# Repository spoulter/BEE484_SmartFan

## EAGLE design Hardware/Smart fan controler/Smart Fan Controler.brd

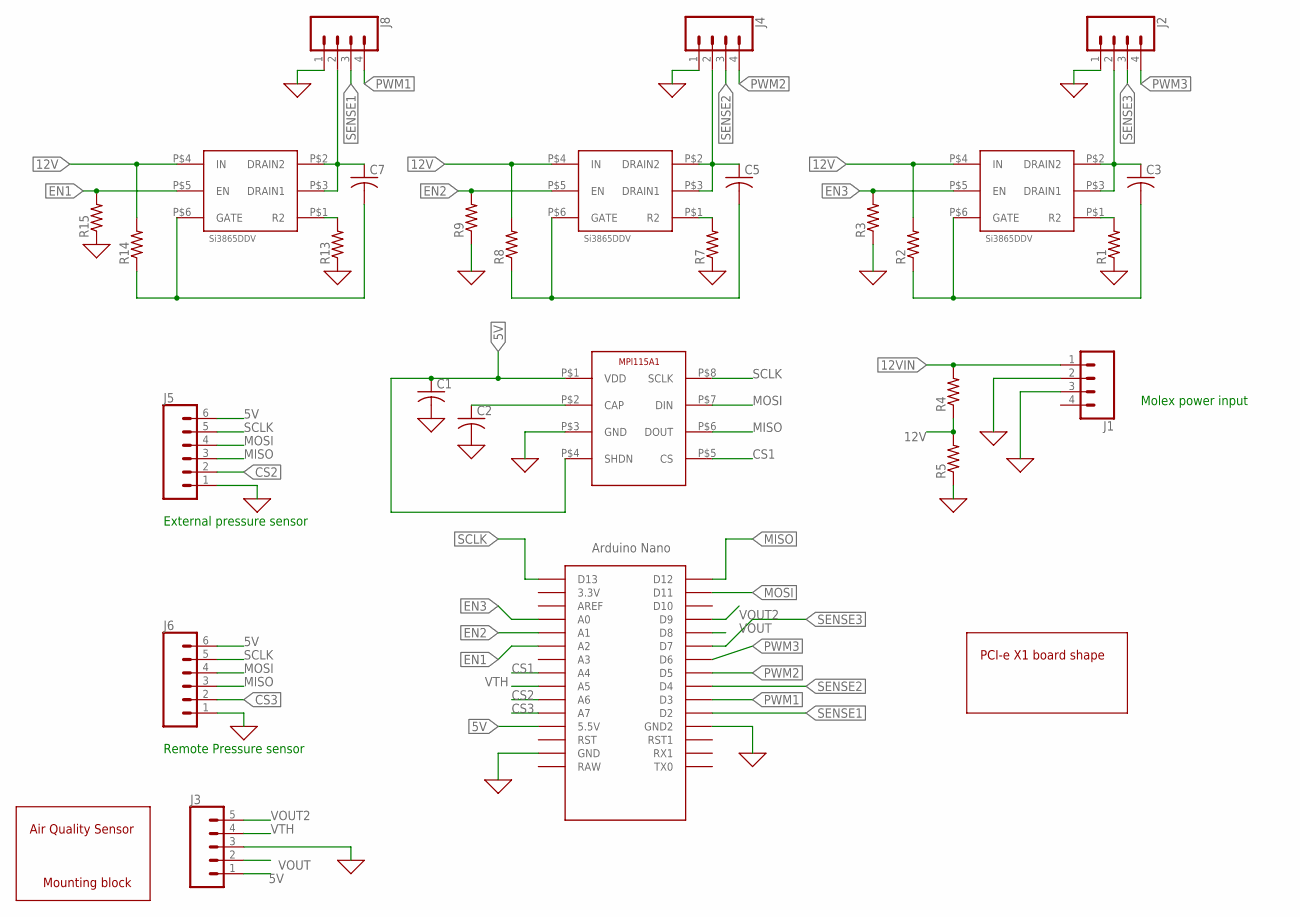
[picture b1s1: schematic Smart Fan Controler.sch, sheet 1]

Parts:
C1, C2, C3, C5, C7: C-USC0805; C0805
J1, J2, J4, J8: CONN_04MOLEX_FAN_HEADER; MOLEX_FAN_HEADER
J3: CONN_05NO_SILK; 1X05_NO_SILK
J5, J6: CONN_06LOCK_LONGPADS; 1X06_LOCK_LONGPADS
R1, R2, R3, R4, R5, R7, R8, R9, R13, R14, R15: R-US_R0805; R0805
U$1: MPL115A1
U$2: NANO
U$3, U$5, U$8: SI3865DDV; TSOP-6
U$4: AIR_QUALITY_SENSOR; AIR_SENSOR

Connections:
0: C1.2, C2.2, J1.2, J1.3, J2.1, J3.3, J4.1, J5.1, J6.1, J8.1, R1.1, R3.1, R5.1, R7.1, R9.1, R13.1, R15.1, U$1.P$3 (GND), U$2.GND, U$2.GND1 (GND2); also elsewhere on the board
5V: C1.1, J3.1, J5.6, J6.6, U$1.P$1 (VDD), U$1.P$4 (SHDN), U$2.5V (5.5V); also elsewhere on the board
12V: R2.2, R4.1, R5.2, R8.2, R14.2, U$3.P$4 (IN), U$5.P$4 (IN), U$8.P$4 (IN)
12VIN: J1.1, R4.2
CS1: U$1.P$5 (CS), U$2.A4
CS2: J5.2, U$2.A6
CS3: J6.2, U$2.A7
EN1: R15.2, U$2.A2, U$8.P$5 (EN)
EN2: R9.2, U$2.A1, U$5.P$5 (EN)
EN3: R3.2, U$2.A0, U$3.P$5 (EN)
MISO: J5.3, J6.3, U$1.P$6 (DOUT), U$2.D12; also elsewhere on the board
MOSI: J5.4, J6.4, U$1.P$7 (DIN), U$2.D11; also elsewhere on the board
unnamed: C2.1, U$1.P$2 (CAP)
unnamed: R1.2, U$3.P$1 (R2)
unnamed: R7.2, U$5.P$1 (R2)
unnamed: C3.1, J2.2, U$3.P$2 (DRAIN2), U$3.P$3 (DRAIN1)
unnamed: C3.2, R2.1, U$3.P$6 (GATE)
unnamed: C5.1, J4.2, U$5.P$2 (DRAIN2), U$5.P$3 (DRAIN1)
unnamed: C5.2, R8.1, U$5.P$6 (GATE)
unnamed: R13.2, U$8.P$1 (R2)
unnamed: C7.1, J8.2, U$8.P$2 (DRAIN2), U$8.P$3 (DRAIN1)
unnamed: C7.2, R14.1, U$8.P$6 (GATE)
PWM1: J8.4, U$2.D3
PWM2: J4.4, U$2.D5
PWM3: J2.4, U$2.D6
SCLK: J5.5, J6.5, U$1.P$8 (SCLK), U$2.D13; also elsewhere on the board
SENSE1: J8.3, U$2.D2
SENSE2: J4.3, U$2.D4
SENSE3: J2.3, U$2.D7
VOUT: J3.2, U$2.D8
VOUT2: J3.5, U$2.D9
VTH: J3.4, U$2.A5

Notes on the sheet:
Molex power input
Remote Pressure sensor
External pressure sensor
PCI-e X1 board shape

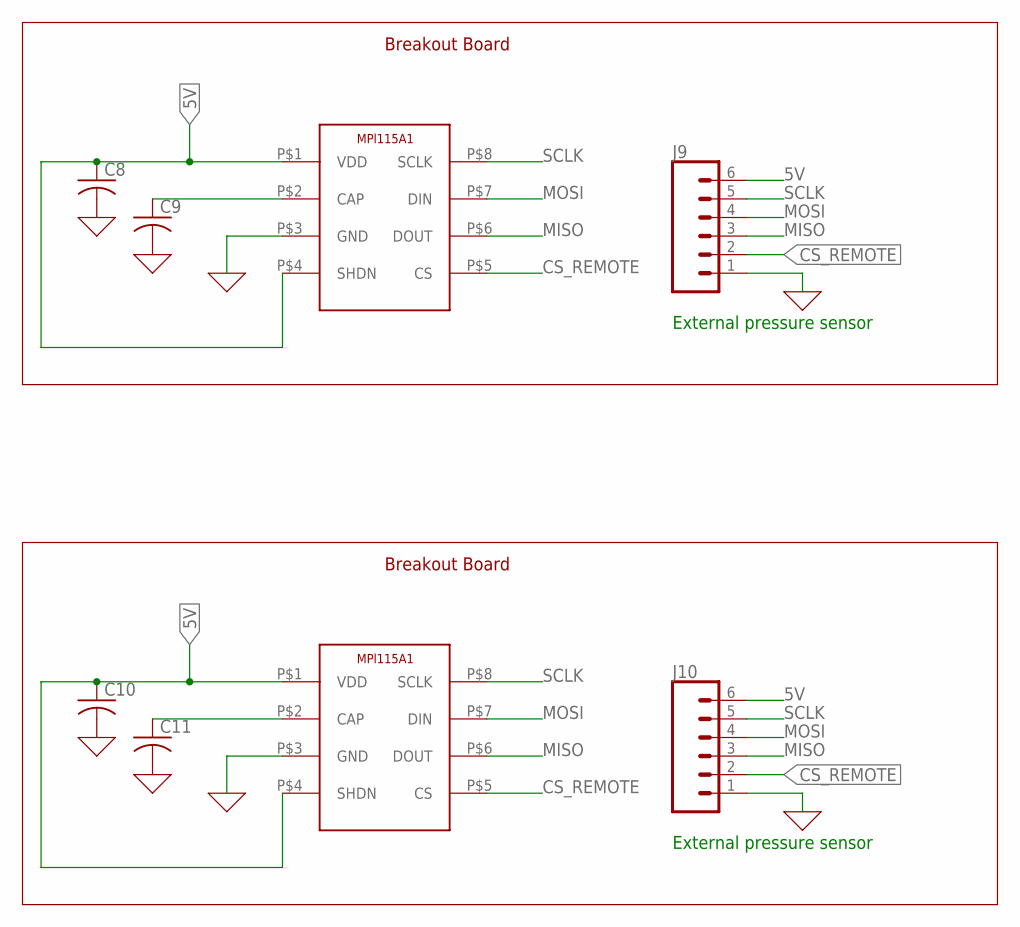
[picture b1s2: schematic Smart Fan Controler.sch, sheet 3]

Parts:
C8, C9, C10, C11: C-USC0805; C0805
J9, J10: CONN_06LOCK_LONGPADS; 1X06_LOCK_LONGPADS
U$7, U$9: MPL115A1

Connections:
0: C8.2, C9.2, C10.2, C11.2, J9.1, J10.1, U$7.P$3 (GND), U$9.P$3 (GND); also elsewhere on the board
5V: C8.1, C10.1, J9.6, J10.6, U$7.P$1 (VDD), U$7.P$4 (SHDN), U$9.P$1 (VDD), U$9.P$4 (SHDN); also elsewhere on the board
CS_REMOTE: J9.2, J10.2, U$7.P$5 (CS), U$9.P$5 (CS)
MISO: J9.3, J10.3, U$7.P$6 (DOUT), U$9.P$6 (DOUT); also elsewhere on the board
MOSI: J9.4, J10.4, U$7.P$7 (DIN), U$9.P$7 (DIN); also elsewhere on the board
unnamed: C9.1, U$7.P$2 (CAP)
unnamed: C11.1, U$9.P$2 (CAP)
SCLK: J9.5, J10.5, U$7.P$8 (SCLK), U$9.P$8 (SCLK); also elsewhere on the board

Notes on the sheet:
External pressure sensor
Breakout Board

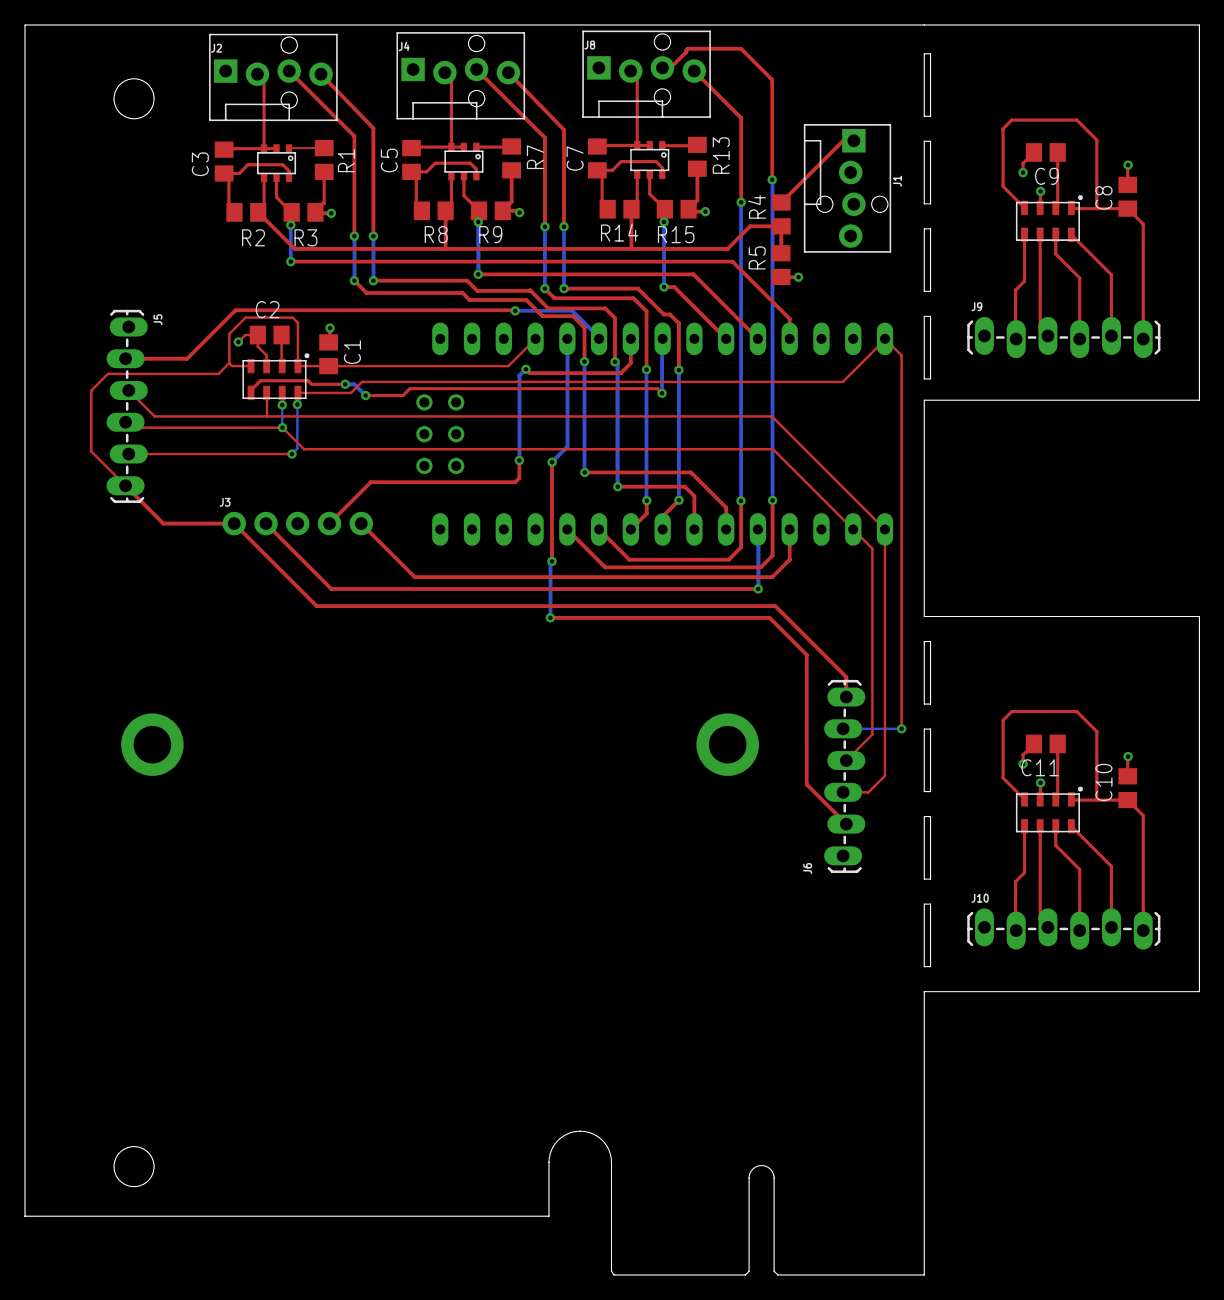
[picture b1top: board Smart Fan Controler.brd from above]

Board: 2 copper layers, 93.9 x 100.0 mm, 37 parts (1 on the bottom side), 35 nets.

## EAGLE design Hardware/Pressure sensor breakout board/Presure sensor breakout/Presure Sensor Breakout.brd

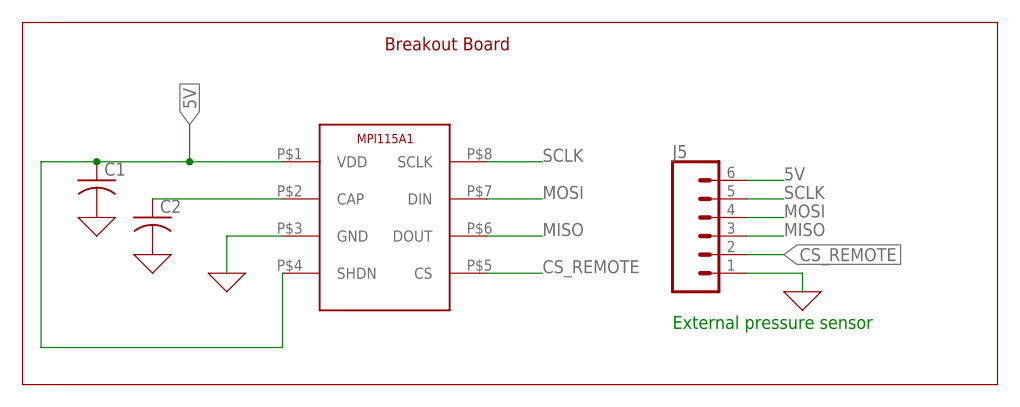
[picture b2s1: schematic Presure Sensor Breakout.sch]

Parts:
C1, C2: C-USC0805; C0805
J5: CONN_06LOCK_LONGPADS; 1X06_LOCK_LONGPADS
U$1: MPL115A1

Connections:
0: C1.2, C2.2, J5.1, U$1.P$3 (GND)
5V: C1.1, J5.6, U$1.P$1 (VDD), U$1.P$4 (SHDN)
CS_REMOTE: J5.2, U$1.P$5 (CS)
MISO: J5.3, U$1.P$6 (DOUT)
MOSI: J5.4, U$1.P$7 (DIN)
unnamed: C2.1, U$1.P$2 (CAP)
SCLK: J5.5, U$1.P$8 (SCLK)

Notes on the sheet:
External pressure sensor
Breakout Board

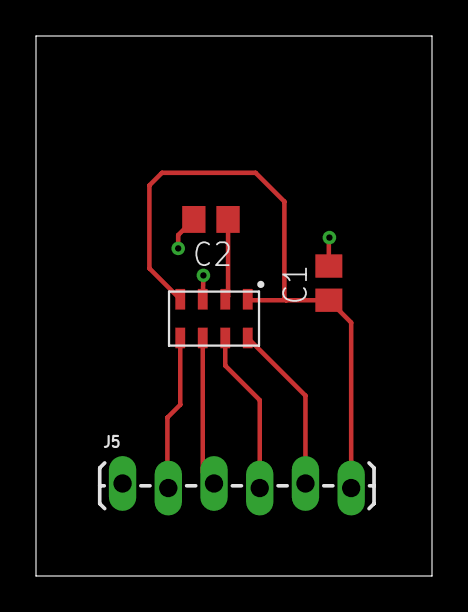
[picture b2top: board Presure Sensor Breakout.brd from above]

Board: 2 copper layers, 22.0 x 30.0 mm, 4 parts (0 on the bottom side), 7 nets.

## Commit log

2018-10-05 Created eagle project file and library. Schemeatic mostly finished
2018-10-05 Reorganized. and added power switch to library
2018-10-06 added datasheet and Bill of Materials
2018-10-06 Removed temporary library
2018-10-06 no message
2018-10-07 Added 3d packages for nano and Fan header. corrected fan header footprint.
2018-10-07 started work on board
2018-10-07 Found fan header in digikey.
2018-10-09 Added 3d model to sensor and fixed fan header 3d model.
2018-10-09 Updated BOM
2018-10-10 Added Mounting holes for bracket
2018-10-11 added 3d models
2018-10-11 Final BOM
2018-10-11 Main board Done
2018-10-12 added stuff.
2018-10-12 added stuff
2018-10-12 added breakout board
2018-10-12 Finalized board
2018-10-12 Added gerber files.
2018-10-18 Finalized board and made gerber files
2018-10-18 uploading version of BOM that was submitted to professor.
2018-10-30 Added Arduino Pin connection refference to software folder
2018-10-30 Added legend to clarify pin connections
2018-11-07 Create Found this online

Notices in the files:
parts and their libraries:
SparkFun-Connectors: Licensing: Creative Commons ShareAlike 4.0 International - https://creativecommons.org/licenses/by-sa/4.0
